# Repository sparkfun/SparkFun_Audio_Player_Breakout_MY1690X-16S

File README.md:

SparkFun Audio Player Breakout - MY1690X-16S
========================================

[*SparkFun Audio Player Breakout - MY1690X-16S (BOB-28038)*](https://www.sparkfun.com/sparkfun-audio-player-breakout-my1690x-16s.html)

The SparkFun M71690X-16S Audio Player Breakout is a compact serial-controlled audio player designed around the MY1690X-16S decoder that supports both .WAV and .MP3 audio files played from a connected microSD card formatted to FAT16 or FAT32. The board includes a USB-C connector to mount it as a removable USB drive on a connected computer, a µSD card slot for connecting a compatible SD card, and a 3.5mm TRRS connector for headphone audio output.

Repository Contents
-------------------

* **.github/workflows** - YAML files used for GitHub Actions and GitHub Pages/mkdocs
* **/Hardware** - KiCad design files (.kicad_pcb, .kicad_sch, .kicad_pro)
  * **/Production** - Production panel files (.kicad_pcb)
* **/docs** - Online documentation files
  * **/assets** - Folder containing all the file assets used for product documentation
    * **/board_files** - Copy of design files used for product documentation
    * **/component_documentation** - Datasheets and manuals for hardware components
    * **/img** - Images for product documentation
  * **/github** - Files stating how to contribute and filing issues used for product documentation
  * **/javascript** - Folder containing custom javascript used for product documentation
  * **/stylesheet** - Folder containing CSS files used for product documentation
* **/overrides** - Customization files used for product documentation
  * **/.icons** - Icons used for GitHub used for product documentation
  * **./partials** - Used for product documentation

Documentation
--------------
* **[SparkFun MY1690X MP3 Decoder Arduino Library](https://github.com/sparkfun/SparkFun_MY1690_MP3_Decoder_Arduino_Library)** - Arduino library for the MY1690X MP3 Decoder.
* **[Hookup Guide](https://docs.sparkfun.com/SparkFun_Audio_Player_Breakout_MY1690X-16S)** - Basic hookup guide for the SparkFun Serial Audio Player Breakout - MY1690X.

Product Versions
----------------
* [BOB-28038](https://www.sparkfun.com/sparkfun-audio-player-breakout-my1690x-16s.html) - v1.0

License Information
-------------------

This product is _**open source**_!

Please review the LICENSE.md file for license information.

If you have any questions or concerns on licensing, please contact technical support on our [SparkFun forums](https://forum.sparkfun.com/viewforum.php?f=152).

Distributed as-is; no warranty is given.

- Your friends at SparkFun.

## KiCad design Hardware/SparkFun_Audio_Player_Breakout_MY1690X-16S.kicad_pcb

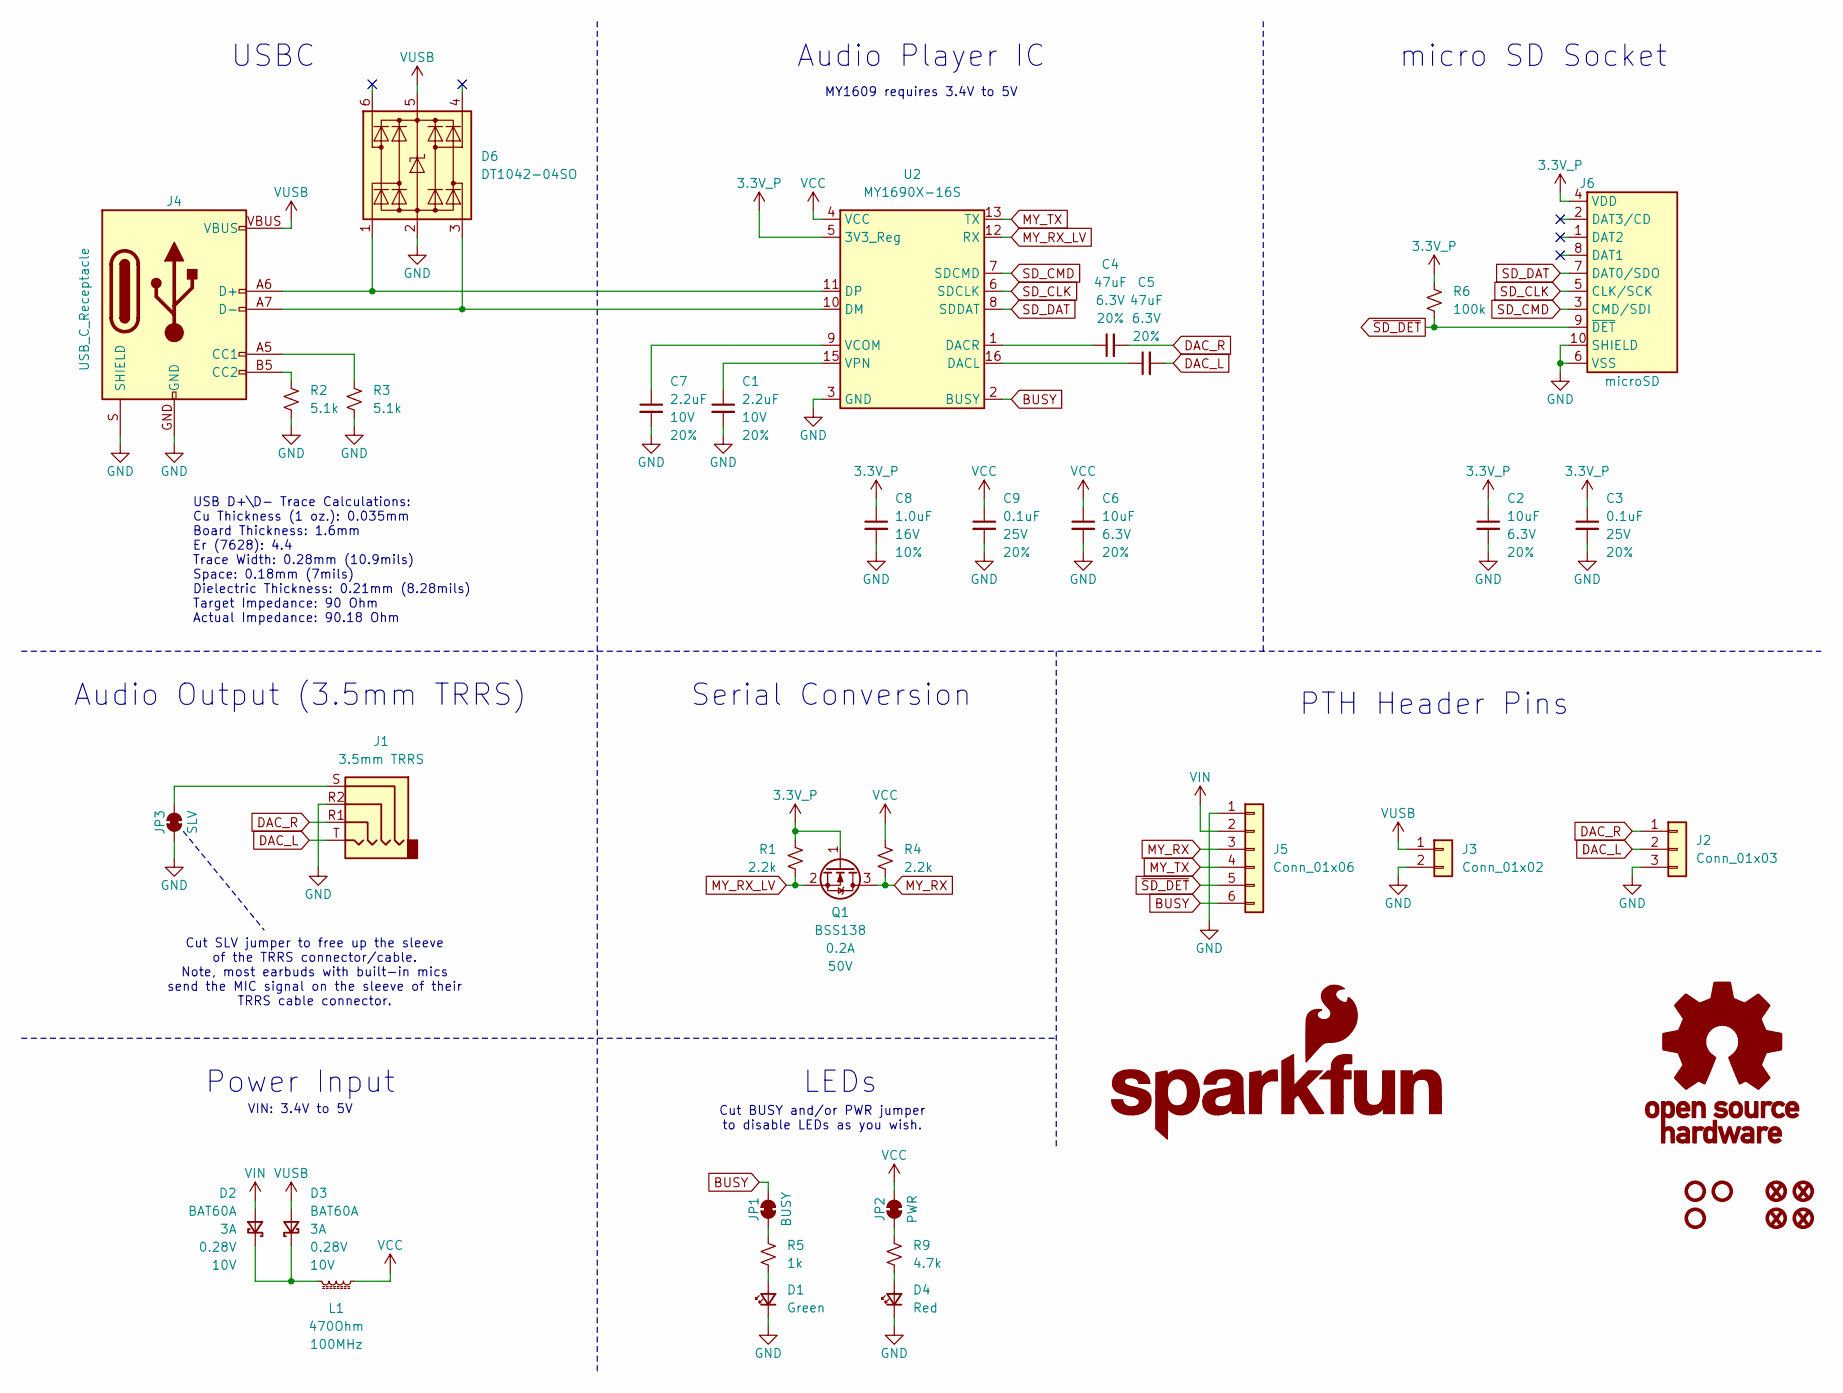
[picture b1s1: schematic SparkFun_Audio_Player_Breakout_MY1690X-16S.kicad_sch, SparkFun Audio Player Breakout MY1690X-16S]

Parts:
C1, C7: 2.2uF; C_0603_1608Metric; Voltage 10V; Tolerance 20%
C2, C6: 10uF; C_0603_1608Metric; Voltage 6.3V; Tolerance 20%
C3, C9: 0.1uF; C_0603_1608Metric; Voltage 25V; Tolerance 20%
C4, C5: 47uF; C_0805_2012Metric; Voltage 6.3V; Tolerance 20%
C8: 1.0uF; C_0603_1608Metric; Voltage 16V; Tolerance 10%
D1: Green; LED_0603_1608Metric_Green
D2, D3: BAT60A; SOD-323
D4: Red; LED_0603_1608Metric_Red
D6: DT1042-04SO; SOT23-6
FID1, FID2, FID3, FID4: Fiducial_0.5mm; Fiducial_0.5mm_Mask1mm
G1: OSHW_Logo; Creative_Commons_License
G5: SparkFun_Logo; SparkFun_Logo_8mm
J1: 3.5mm TRRS; Audio_Jack_3.5mm_TRRS_SMD_RA
J2: Conn_01x03; 1x03
J3: Conn_01x02; 1x02
J4: USB_C_Receptacle; USB-C_16
J5: Conn_01x06; 1x06
J6: microSD; microSD_External_Pin
JP1: BUSY; Jumper_2_NC_Trace
JP2: PWR; Jumper_2_NC_Trace
JP3: SLV; Jumper_2_NC_Trace
L1: 470Ohm; C_0603_1608Metric
Q1: BSS138; SOT23-3
R1, R4: 2.2k; R_0603_1608Metric
R2, R3: 5.1k; R_0603_1608Metric
R5: 1k; R_0603_1608Metric
R6: 100k; R_0603_1608Metric
R9: 4.7k; R_0603_1608Metric
ST1, ST2, ST3: Standoff
U2: MY1690X-16S; SO-16

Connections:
3.3V_P: C2.1, C3.1, C8.1, J6.4 (VDD), Q1.1 (G), R1.2, R6.1, U2.5 (3V3_Reg)
BUSY: J5.6, JP1.2 (B), U2.2 (BUSY)
DAC_L: C5.2, J1.T, J2.2
DAC_R: C4.2, J1.R1, J2.1
GND: C1.2, C2.2, C3.2, C6.2, C7.2, C8.2, C9.2, D1.1 (K), D4.1 (K), D6.2 (GND), J1.R2, J2.3, J3.2, J4.GND, J4.S (SHIELD), J5.1, J6.6 (VSS), J6.10 (SHIELD), JP3.1 (A), R2.2, R3.1, U2.3 (GND), U2.14 (GND)
MY_RX: J5.3, Q1.3 (D), R4.1
MY_RX_LV: Q1.2 (S), R1.1, U2.12 (RX)
MY_TX: J5.4, U2.13 (TX)
unnamed: D1.2 (A), R5.1
unnamed: D2.1 (K), D3.1 (K), L1.2
unnamed: D4.2 (A), R9.1
unnamed: D6.1 (I/O1), J4.A6 (D+), J4.B6 (D+), U2.11 (DP)
unnamed: D6.3 (I/O2), J4.A7 (D-), J4.B7 (D-), U2.10 (DM)
unnamed: J4.A5 (CC1), R3.2
unnamed: J4.B5 (CC2), R2.1
unnamed: JP1.1 (A), R5.2
unnamed: JP2.1 (A), R9.2
unnamed: J1.S, JP3.2 (B)
unnamed: C5.1, U2.16 (DACL)
unnamed: C4.1, U2.1 (DACR)
unnamed: C7.1, U2.9 (VCOM)
unnamed: C1.1, U2.15 (VPN)
SD_CLK: J6.5 (CLK/SCK), U2.6 (SDCLK)
SD_CMD: J6.3 (CMD/SDI), U2.7 (SDCMD)
SD_DAT: J6.7 (DAT0/SDO), U2.8 (SDDAT)
VCC: C6.1, C9.1, JP2.2 (B), L1.1, R4.2, U2.4 (VCC)
VIN: D2.2 (A), J5.2
VUSB: D3.2 (A), D6.5 (VCC), J3.1, J4.VBUS
~SD_DET: J5.5, J6.9 (~DET), R6.2

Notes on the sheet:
USBC
Serial Conversion
MY1609 requires 3.4V to 5V
Audio Output (3.5mm TRRS)
Cut BUSY and/or PWR jumper to disable LEDs as you wish.
micro SD Socket
Power Input
PTH Header Pins
Audio Player IC
LEDs
Cut SLV jumper to free up the sleeve of the TRRS connector/cable. Note, most earbuds with built-in mics send the MIC signal on the sleeve of their TRRS cable connector.
USB D+\D- Trace Calculations: Cu Thickness (1 oz.): 0.035mm Board Thickness: 1.6mm Er (7628): 4.4 Trace Width: 0.28mm (10.9mils) Space: 0.18mm (7mils) Dielectric Thickness: 0.21mm (8.28mils) Target Impedance: 90 Ohm Actual Impedance: 90.18 Ohm
VIN: 3.4V to 5V

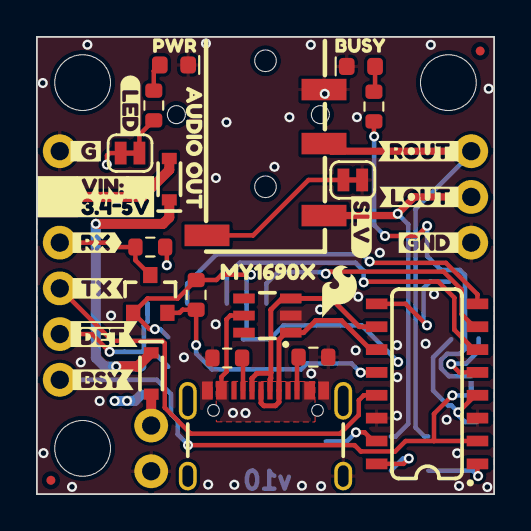
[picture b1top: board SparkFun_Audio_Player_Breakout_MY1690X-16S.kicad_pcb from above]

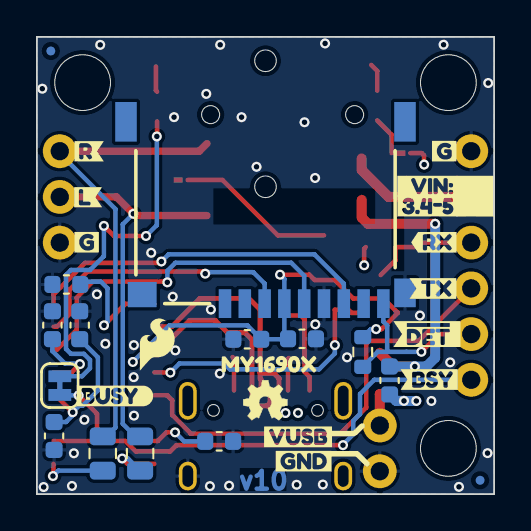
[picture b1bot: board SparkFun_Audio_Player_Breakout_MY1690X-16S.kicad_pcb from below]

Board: 4 copper layers, 25.4 x 25.4 mm, 72 parts (30 on the bottom side), 29 nets.

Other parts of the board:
Ref**: Val**; OSHW_Logo_2.5mm
kibuzzard-67AD02A2: G***; kibuzzard-67AD02A2
kibuzzard-67AD02AA: G***; kibuzzard-67AD02AA
kibuzzard-67AD03CF: G***; kibuzzard-67AD03CF
kibuzzard-67AD03ED: G***; kibuzzard-67AD03ED
kibuzzard-67B388A6: G***; kibuzzard-67B388A6
kibuzzard-67B391D1: G***; kibuzzard-67B391D1
kibuzzard-67B391E8: G***; kibuzzard-67B391E8
kibuzzard-67B394D8: G***; kibuzzard-67B394D8
kibuzzard-67B3920A: G***; kibuzzard-67B3920A
kibuzzard-67B38923: G***; kibuzzard-67B38923
kibuzzard-67B39233: G***; kibuzzard-67B39233
kibuzzard-67B39251: G***; kibuzzard-67B39251
kibuzzard-67B39267: G***; kibuzzard-67B39267
kibuzzard-6792C5B0: G***; kibuzzard-6792C5B0
kibuzzard-6792C5D2: G***; kibuzzard-6792C5D2
kibuzzard-6792C7DD, kibuzzard-6792C7DD#2: G***; kibuzzard-6792C7DD
kibuzzard-6792C876, kibuzzard-6792C876#2: G***; kibuzzard-6792C876
kibuzzard-6792CAB7: G***; kibuzzard-6792CAB7
kibuzzard-6792CAD9: G***; kibuzzard-6792CAD9
kibuzzard-6792CB45: G***; kibuzzard-6792CB45
kibuzzard-6792CB58: G***; kibuzzard-6792CB58
kibuzzard-6792CCE2: G***; kibuzzard-6792CCE2
kibuzzard-6792CD0E: G***; kibuzzard-6792CD0E
kibuzzard-6792CF5F: G***; kibuzzard-6792CF5F
kibuzzard-6792CF7B: G***; kibuzzard-6792CF7B
kibuzzard-6792CF8E: G***; kibuzzard-6792CF8E
kibuzzard-6798FF71: G***; kibuzzard-6798FF71
kibuzzard-679417DC: G***; kibuzzard-679417DC

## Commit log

2025-01-23 parts placed for a 1x1
2025-01-23 update git ignore
2025-01-24 re-order header pins to put GND/VIN/RX/TX in a row
2025-01-24 TVS diode SOT23-6 package
    -for easier production/rework
2025-01-24 Routed v01 (pre-review)
2025-01-24 datasheet
2025-01-28 review changes 1
    -TX bottom silk fishtail (output)
    -centered position of OSHW logo
    -nudged vcc vias near VUSB pth headers for better ground flow pour
    -named JP3 "SLV"
    -added jumper comments to sch
    -moved C1/C8 to avoid text overlap in SCH
2025-01-28 removed R6 pull-down on uSD CLK line
2025-01-28 review changes 2
    -rotated LED jumper for easier access to cut when headers are populated
    -repositioned bottom passive components under the USB (now that R6 is gone). This allows bypass caps to be closer to uSD card pins.
    -updated frame info on brd and sch
2025-01-28 repositioned connectors to have over-hang
2025-01-29 checklist eng run
    -added ordering instruction about NPTH holes (under the TRRS connector)
    -sch cleanup
    -add VIN range in SCH and BRD
    -add "1234" text objects to each layer
    -nudges a via under LOUT silk
2025-01-29 Moved PCB version to under USB conn
    -it was getting blocked by the uSD card socket
2025-01-29 removed 1234 in copper
2025-01-29 one more via
    -added GND via next to double VCC via to inner plane
2025-01-29 prototype gerbers v01
2025-02-03 v01 assembly sheets - top & bottom
2025-02-04 Clean up clone for product
2025-02-17 Post-proto testing changes - v10
    -bumped version to v10 in sch and brd
    -added 3.4-5V in buzzard labels at the header pin
    -added over-bar to sd detect silk
    -added pullup resistor on sd detect
    -Move 3.3V_P trace elsewhere to avoid coupling and keep a complete plane (VCC) under the USB D+/D- lines.
2025-02-17 Sch cleanup
    -change title block texts to standard color and boldness
2025-02-18 checklist reds eng v10
    -update measures
    -update kicad layer naming to new standards
2025-02-18 soldermask color RED
2025-02-18 updated version in page settings on PCB file
2025-02-19 USB trace tweaks
    -added USB trace calculations to SCH
    -general sch cleanup and spacing
    -adjusted USB data traces from 10mils to 9.7mils
    -adjusted USB data traces routing for proper 7mil gap
2025-02-19 updated layer names to new standards
2025-02-19 production panel and gerbers v10
2025-02-19 corrected USB trace width calcs
    -Prepeg is actually 8.28mils, not 7.1, according to Fab houses specs.
    -adjusted calcs/traces/gaps
2025-02-19 updated production panel and gerbers v10
2025-02-19 renaming ZIP file to include version v10
2025-02-20 v10b gerbers
    -increased panel horizontal gaps from 0.2inches to 0.3inches for optimizing new AOI machine.
    -removed individual gerber files to clean up repo (only really need the ZIP)
    -renamed ZIP to include v10b, to keep versions straight on gerbers.
    -removed v10 older gerbers.
2025-02-20 Ordering instructions updated - panel/gerber v10c
    -Material TG135-140
    -Controlled Impedance: No
2025-04-08 Documentation commit
    Updating from template. Adding all content & photos after initial review.
2025-04-09 Adding build workflows
    Adding build_documentation.yml
2025-04-09 Deployed b86b60c with MkDocs version: 1.6.1
2025-04-09 Update README.md
    Adding photo, description & updating links.
2025-04-09 Deployed b391da8 with MkDocs version: 1.6.1
2025-04-15 Minor docs update
    Adding missing logo & thumbnail assets and fixing copy/paste errors in contribute & file issue files.
2025-04-15 Deployed 20dd9af with MkDocs version: 1.6.1

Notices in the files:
parts and their libraries:
https://creativecommons.org/licenses/by-sa/4.0
Released under the Creative Commons Attribution Share-Alike 4.0 License
